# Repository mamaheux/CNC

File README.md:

# CNC
This is a project to learn how to create a 3-axis CNC router. It contains the mechanical, electrical and software designs.

## Folder Descriptions

### CAD
This folder contains the CAD files to build the CNC. It is built from aluminium extrusions and 3D printed parts.

### control
This folder contains the graphical user interface for controlling the CNC from a computer.

### electronics/teensy
This folder contains the PCB design of the board controlling the stepper drivers, endstops, and spindle drive.

### firmware
This folder contains the firmware that parses the G-code to control the spindle speed and the stepper motors using a trapezoidal velocity profile.

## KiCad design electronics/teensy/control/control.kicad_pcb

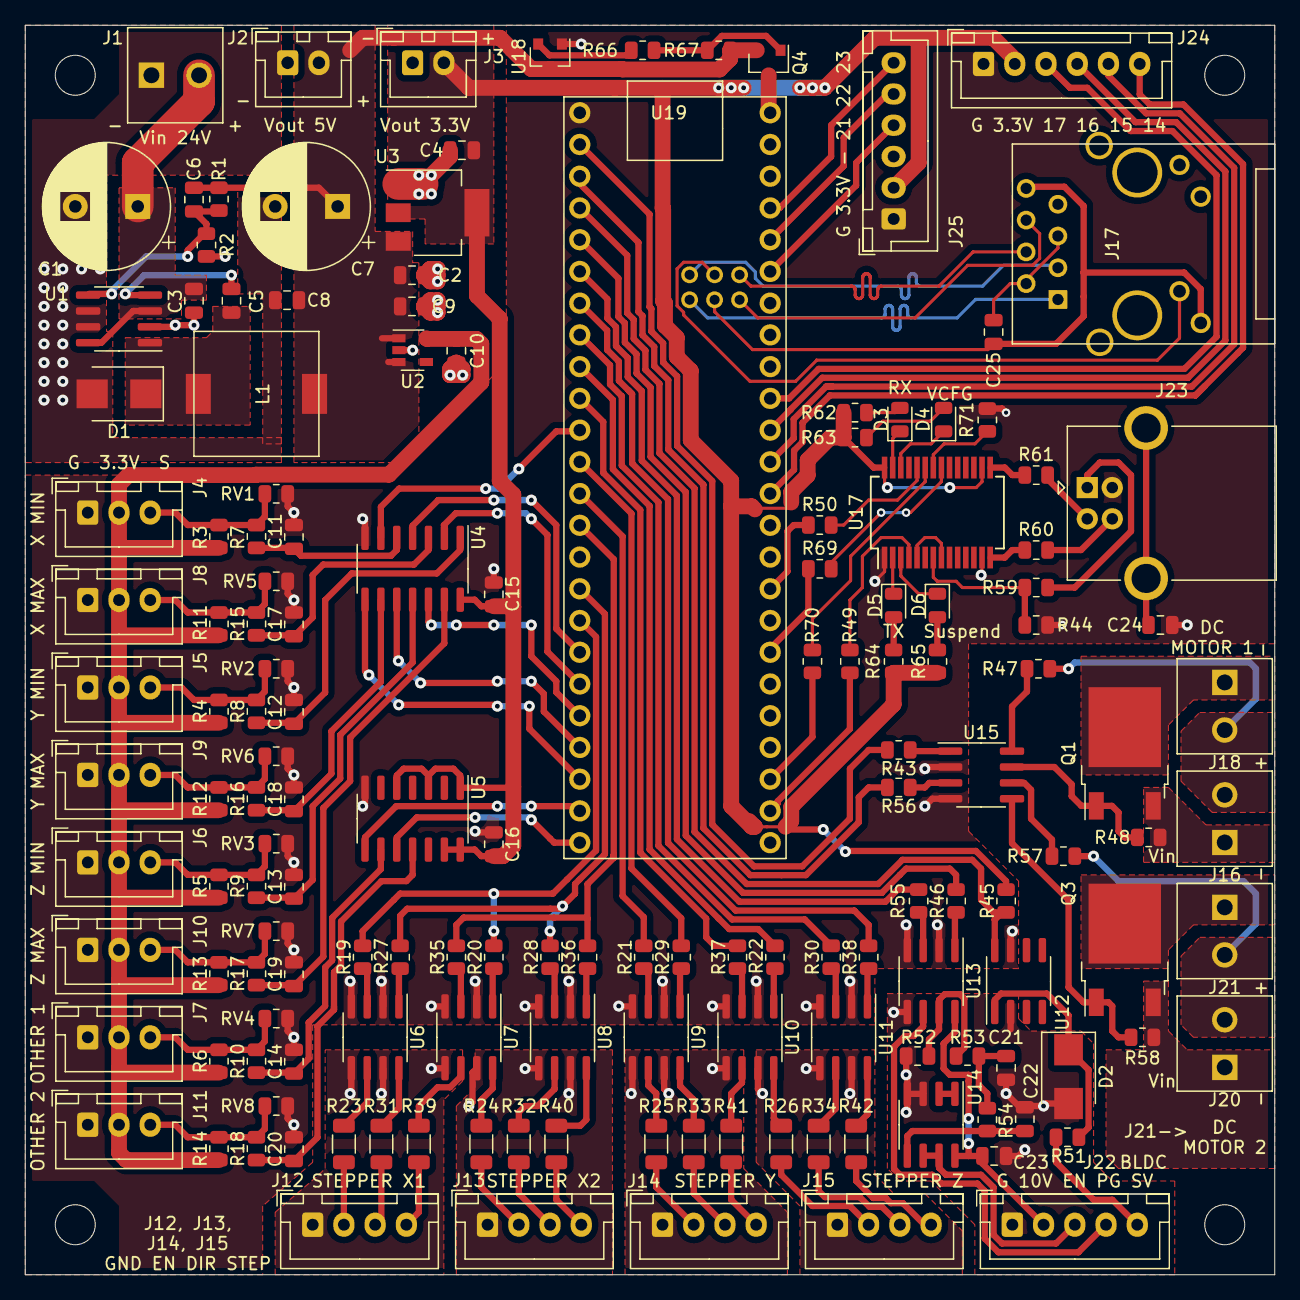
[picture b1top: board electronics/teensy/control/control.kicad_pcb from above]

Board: 2 copper layers, 100.0 x 100.0 mm, 156 parts (1 on the bottom side), 153 nets.

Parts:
C1: 33µF/35V; CP_Radial_D10.0mm_P5.00mm
C2: 10µF/10V/Low ESL; C_0805_2012Metric
C3, C9, C10, C23: 1µF/35V; C_0805_2012Metric
C4: 22µF/10V/Low ESL; C_0805_2012Metric
C5: 0.33µF; C_0805_2012Metric
C6, C11, C12, C13, C14, C15, C16, C17, C18, C19, C20, C22, C25: 0.1µF/25V; C_0805_2012Metric
C7: 330µF/10V; CP_Radial_D10.0mm_P5.00mm
C8: 2.2µF/35V; C_0805_2012Metric
C21: 47nF/25V; C_0805_2012Metric
C24: 4700pF; C_0805_2012Metric
D1, D2: B340AE-13; D_SMB
D3: ORANGE; D_0805_2012Metric
D4: GREEN; D_0805_2012Metric
D5: BLUE; D_0805_2012Metric
D6: RED; D_0805_2012Metric
J1: Vin 24V; EBWA-02-B
J2: Vout 5V; JST_XH_B2B-XH-A_1x02_P2.50mm_Vertical
J3: Vout 3.3V; JST_XH_B2B-XH-A_1x02_P2.50mm_Vertical
J4: X_MIN; JST_XH_B3B-XH-A_1x03_P2.50mm_Vertical
J5: Y_MIN; JST_XH_B3B-XH-A_1x03_P2.50mm_Vertical
J6: Z_MIN; JST_XH_B3B-XH-A_1x03_P2.50mm_Vertical
J7: OTHER 1; JST_XH_B3B-XH-A_1x03_P2.50mm_Vertical
J8: X_MAX; JST_XH_B3B-XH-A_1x03_P2.50mm_Vertical
J9: Y_MAX; JST_XH_B3B-XH-A_1x03_P2.50mm_Vertical
J10: Z_MAX; JST_XH_B3B-XH-A_1x03_P2.50mm_Vertical
J11: OTHER_2; JST_XH_B3B-XH-A_1x03_P2.50mm_Vertical
J12, J14, J15: Stepper X1; JST_XH_B4B-XH-A_1x04_P2.50mm_Vertical
J13: Stepper X2; JST_XH_B4B-XH-A_1x04_P2.50mm_Vertical
J16, J20: DC Motor Vin 24V; EBWA-02-B
J17: Cetus_J1B1211CCD; Cetus J1B1211CCD
J18, J21: DC Motor; EBWA-02-B
J22: SPINDLE_BLDC_CONTROLLER; JST_XH_B5B-XH-A_1x05_P2.50mm_Vertical
J23: USB_B; USB_B_OST_USB-B1HSxx_Horizontal
J24, J25: EXT; JST_XH_B6B-XH-A_1x06_P2.50mm_Vertical
L1: 68µH/Sumida CDRH104R-680MC; CDRH104RNP-680NC
Q1, Q3: TK1R4S04PB; TO-252-2
Q4: SI2301CDS-T1-E3; SOT-23
R1: 3.01k; R_0805_2012Metric
R2: 976; R_0805_2012Metric
R3, R4, R5, R6, R7, R8, R9, R10, R11, R12, R13, R14, R15, R16, R17, R18, R45, R47, R48, R57, R58, R59, R66: 10k; R_0805_2012Metric
R19, R20, R21, R22, R27, R28, R29, R30, R35, R36, R37, R38, R43, R46, R49, R50, R51, R55, R56, R69, R70, R71: 1k; R_0805_2012Metric
R23, R24, R25, R26, R31, R32, R33, R34, R39, R40, R41, R42: 1.82k/0.5W; R_1206_3216Metric
R44: 20k; R_0805_2012Metric
R52: 2.2k; R_0805_2012Metric
R53: 47k; R_0805_2012Metric
R54, R67: 100k; R_0805_2012Metric
R60, R61: 24; R_0805_2012Metric
R62: 174; R_0805_2012Metric
R63, R65: 150; R_0805_2012Metric
R64: 30.1; R_0805_2012Metric
R68: 0; R_1206_3216Metric
RV1, RV2, RV3, RV4, RV5, RV6, RV7, RV8: VC080503A100DP; R_0805_2012Metric
U1: MIC4684; SOIC-8_3.9x4.9mm_P1.27mm
U2: AP7354-33W5-7; SOT-23-5
U3: AZ1117IH-3.3TRG1; SOT-223-3_TabPin2
U4, U5: SN74LVC14ADRG3; SOIC-14_3.9x8.7mm_P1.27mm
U6, U7, U8, U9, U10, U11, U12, U13, U15: MOCD217R2M; SOIC-8_3.9x4.9mm_P1.27mm
U14: TS912; SOIC-8_3.9x4.9mm_P1.27mm
U17: CY7C64225; SSOP-28_5.3x10.2mm_P0.65mm
U18: LM810M3-4.63; SOT-23
U19: Teensy_4.1; Teensy 4.1

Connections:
+3V3: C4.1, C15.1, C16.1, J3.2, J24.2, J25.2, R45.2, R62.1, R63.1, R64.1, R65.1, U3.2, U4.14, U5.1, U5.3, U5.5, U5.13, U5.14, U17.16, U17.28
+3V3_LSW: C10.1, J4.2, J5.2, J6.2, J7.2, J8.2, J9.2, J10.2, J11.2, R3.1, R4.1, R5.1, R6.1, R11.1, R12.1, R13.1, R14.1, U2.5
+5V: C2.1, C6.1, C7.1, C8.1, C9.1, J2.2, L1.2, Q4.2, R1.1, R67.2, U2.1, U2.3, U3.3, U18.3
+24V: C1.1, C3.1, J1.2, U1.3, U1.8
/endstops/X_MAX: U4.4, U19.26
/endstops/X_MIN: U4.6, U19.9
/endstops/Y_MAX: U4.8, U19.30
/endstops/Y_MIN: U4.2, U19.27
/endstops/Z_MAX: U4.12, U19.28
/endstops/Z_MIN: U4.10, U19.29
/mcu/BLDC_MOTOR_PWM: R46.2, U19.3
/mcu/DC_MOTOR_PWM_1: R43.2, U19.0
/mcu/DC_MOTOR_PWM_2: R56.2, U19.1
/mcu/ETH_GND: C25.2, J17.8, J17.9, U19.ETH_GND
/mcu/ETH_LED: J17.10, U19.ETH_LED
/mcu/ETH_RX+: J17.4, U19.ETH_RX+
/mcu/ETH_RX-: J17.6, U19.ETH_RX-
/mcu/ETH_TX+: J17.1, U19.ETH_TX+
/mcu/ETH_TX-: J17.3, U19.ETH_TX-
/mcu/OTHER_1_ENDSTOP: U5.8, U19.31
/mcu/OTHER_2_ENDSTOP: U5.10, U19.32
/mcu/PIN_14: J24.6, U19.14
/mcu/PIN_15: J24.5, U19.15
/mcu/PIN_16: J24.4, U19.16
/mcu/PIN_17: J24.3, U19.17
/mcu/PIN_21: J25.4, U19.21
/mcu/PIN_22: J25.5, U19.22
/mcu/PIN_23: J25.6, U19.23
/mcu/USB_UART_CTS: R69.1, U19.39
/mcu/USB_UART_RTS: R50.1, U19.41
/mcu/USB_UART_RX: R70.1, U19.35
/mcu/USB_UART_TX: R49.1, U19.34
/spindle/BLDC_CONTROLLER_10V: C23.1, J22.2, U13.8, U14.8
/spindle/BLDC_CONTROLLER_EN: J22.4, U13.6
/spindle/BLDC_CONTROLLER_GND: C21.2, C22.2, C23.2, D2.2, J22.1, R52.2, U12.2, U13.5, U14.3, U14.4
/spindle/BLDC_CONTROLLER_PG: J22.5, R51.1
/spindle/BLDC_CONTROLLER_SV: J22.3, U14.6, U14.7
/spindle/BLDC_EN: R55.2, U19.4
/spindle/BLDC_FEEDBACK: R45.1, U12.8, U19.2
/spindle/DC_MOTOR_24V_1: J16.2, J18.2, R47.2
/spindle/DC_MOTOR_24V_2: J20.2, J21.2, R57.2
/spindle/DC_MOTOR_GND_1: J16.1, Q1.3, R48.1
/spindle/DC_MOTOR_GND_2: J20.1, Q3.3, R58.1
/steppers/OPTO_X_DIR_1: J12.3, R31.1
/steppers/OPTO_X_DIR_2: J13.3, R32.1
/steppers/OPTO_X_EN_1: J12.2, R23.1
/steppers/OPTO_X_EN_2: J13.2, R24.1
/steppers/OPTO_X_GND_1: J12.1, U6.5, U6.7, U7.5
/steppers/OPTO_X_GND_2: J13.1, U7.7, U8.5, U8.7
/steppers/OPTO_X_STEP_1: J12.4, R39.1
/steppers/OPTO_X_STEP_2: J13.4, R40.1
/steppers/OPTO_Y_DIR: J14.3, R33.1
/steppers/OPTO_Y_EN: J14.2, R25.1
/steppers/OPTO_Y_GND: J14.1, U9.5, U9.7, U10.5
/steppers/OPTO_Y_STEP: J14.4, R41.1
/steppers/OPTO_Z_DIR: J15.3, R34.1
/steppers/OPTO_Z_EN: J15.2, R26.1
/steppers/OPTO_Z_GND: J15.1, U10.7, U11.5, U11.7
/steppers/OPTO_Z_STEP: J15.4, R42.1
/steppers/X_DIR: R27.2, R28.2, U19.24
/steppers/X_EN: R19.2, R20.2, U19.25
/steppers/X_STEP: R35.2, R36.2, U19.12
/steppers/Y_DIR: R29.2, U19.10
/steppers/Y_EN: R21.2, U19.11
/steppers/Y_STEP: R37.2, U19.8
/steppers/Z_DIR: R30.2, U19.6
/steppers/Z_EN: R22.2, U19.7
/steppers/Z_STEP: R38.2, U19.5
GNDD: C11.2, C12.2, C13.2, C14.2, C15.2, C16.2, C17.2, C18.2, C19.2, C20.2, C24.2, J4.1, J5.1, J6.1, J7.1, J8.1, J9.1, J10.1, J11.1, J23.4, J24.1, J25.1, R44.2, R68.2, R71.2, RV1.1, RV2.1, RV3.1, RV4.1, RV5.1, RV6.1, RV7.1, RV8.1, U4.7, U5.7, U6.2, U6.4, U7.2, U7.4, U8.2, U8.4, U9.2, U9.4, U10.2, U10.4, U11.2, U11.4, U12.7, U13.2, U13.4, U15.2, U15.4, U17.1, U17.13, U18.1, U19.GND_0
GNDPWR: C1.2, C2.2, C3.2, C4.2, C7.2, C8.2, C9.2, C10.2, D1.2, J1.1, J2.1, J3.1, R2.2, R68.1, U1.2, U1.6, U1.7, U2.2, U3.1
unnamed: C5.1, U1.4
unnamed: C5.2, D1.1, L1.1, U1.1
unnamed: C6.2, R1.2, R2.1, U1.5
unnamed: C11.1, R7.1, U4.5
unnamed: C12.1, R8.1, U4.1
unnamed: C13.1, R9.1, U4.11
unnamed: C14.1, R10.1, U5.9
unnamed: C17.1, R15.1, U4.3
unnamed: C18.1, R16.1, U4.9
unnamed: C19.1, R17.1, U4.13
unnamed: C20.1, R18.1, U5.11
unnamed: C21.1, R53.1, R54.2
unnamed: C22.1, R54.1, U14.5
unnamed: C24.1, J23.5
unnamed: C25.1, J17.2, J17.5
unnamed: D2.1, R51.2, U12.1
unnamed: D3.1, U17.27
unnamed: D3.2, R62.2
unnamed: D4.1, U17.26
unnamed: D4.2, R63.2
unnamed: D5.1, U17.2
unnamed: D5.2, R64.2
unnamed: D6.1, U17.3
unnamed: D6.2, R65.2
unnamed: J4.3, R3.2, R7.2, RV1.2
unnamed: J5.3, R4.2, R8.2, RV2.2
unnamed: J6.3, R5.2, R9.2, RV3.2
unnamed: J7.3, R6.2, R10.2, RV4.2
unnamed: J8.3, R11.2, R15.2, RV5.2
unnamed: J9.3, R12.2, R16.2, RV6.2
unnamed: J10.3, R13.2, R17.2, RV7.2
unnamed: J11.3, R14.2, R18.2, RV8.2
unnamed: J18.1, Q1.2
unnamed: J21.1, Q3.2
unnamed: J23.1, R59.2
unnamed: J23.2, R61.2
unnamed: J23.3, R60.2
unnamed: Q1.1, R48.2, U15.7
unnamed: Q3.1, R58.2, U15.5
unnamed: Q4.1, R66.1, R67.1
unnamed: Q4.3, U19.Vin
unnamed: R19.1, U6.3
unnamed: R20.1, U7.1
unnamed: R21.1, U9.3
unnamed: R22.1, U10.1
unnamed: R23.2, U6.6
unnamed: R24.2, U7.8
unnamed: R25.2, U9.6
unnamed: R26.2, U10.8
unnamed: R27.1, U6.1
unnamed: R28.1, U8.3
unnamed: R29.1, U9.1
unnamed: R30.1, U11.3
unnamed: R31.2, U6.8
unnamed: R32.2, U8.6
unnamed: R33.2, U9.8
unnamed: R34.2, U11.6
unnamed: R35.1, U7.3
unnamed: R36.1, U8.1
unnamed: R37.1, U10.3
unnamed: R38.1, U11.1
unnamed: R39.2, U7.6
unnamed: R40.2, U8.8
unnamed: R41.2, U10.6
unnamed: R42.2, U11.8
unnamed: R43.1, U15.1
unnamed: R44.1, R59.1, U17.7
unnamed: R46.1, U13.1
unnamed: R47.1, U15.8
unnamed: R49.2, U17.4
unnamed: R50.2, U17.24
unnamed: R52.1, R53.2, U13.7
unnamed: R55.1, U13.3
unnamed: R56.1, U15.3
unnamed: R57.1, U15.6
unnamed: R60.1, U17.14
unnamed: R61.1, U17.15
unnamed: R66.2, U18.2
unnamed: R69.2, U17.21
unnamed: R70.2, U17.23
unnamed: R71.1, U17.22
unnamed: U14.1, U14.2
unnamed: U17.5, U17.8

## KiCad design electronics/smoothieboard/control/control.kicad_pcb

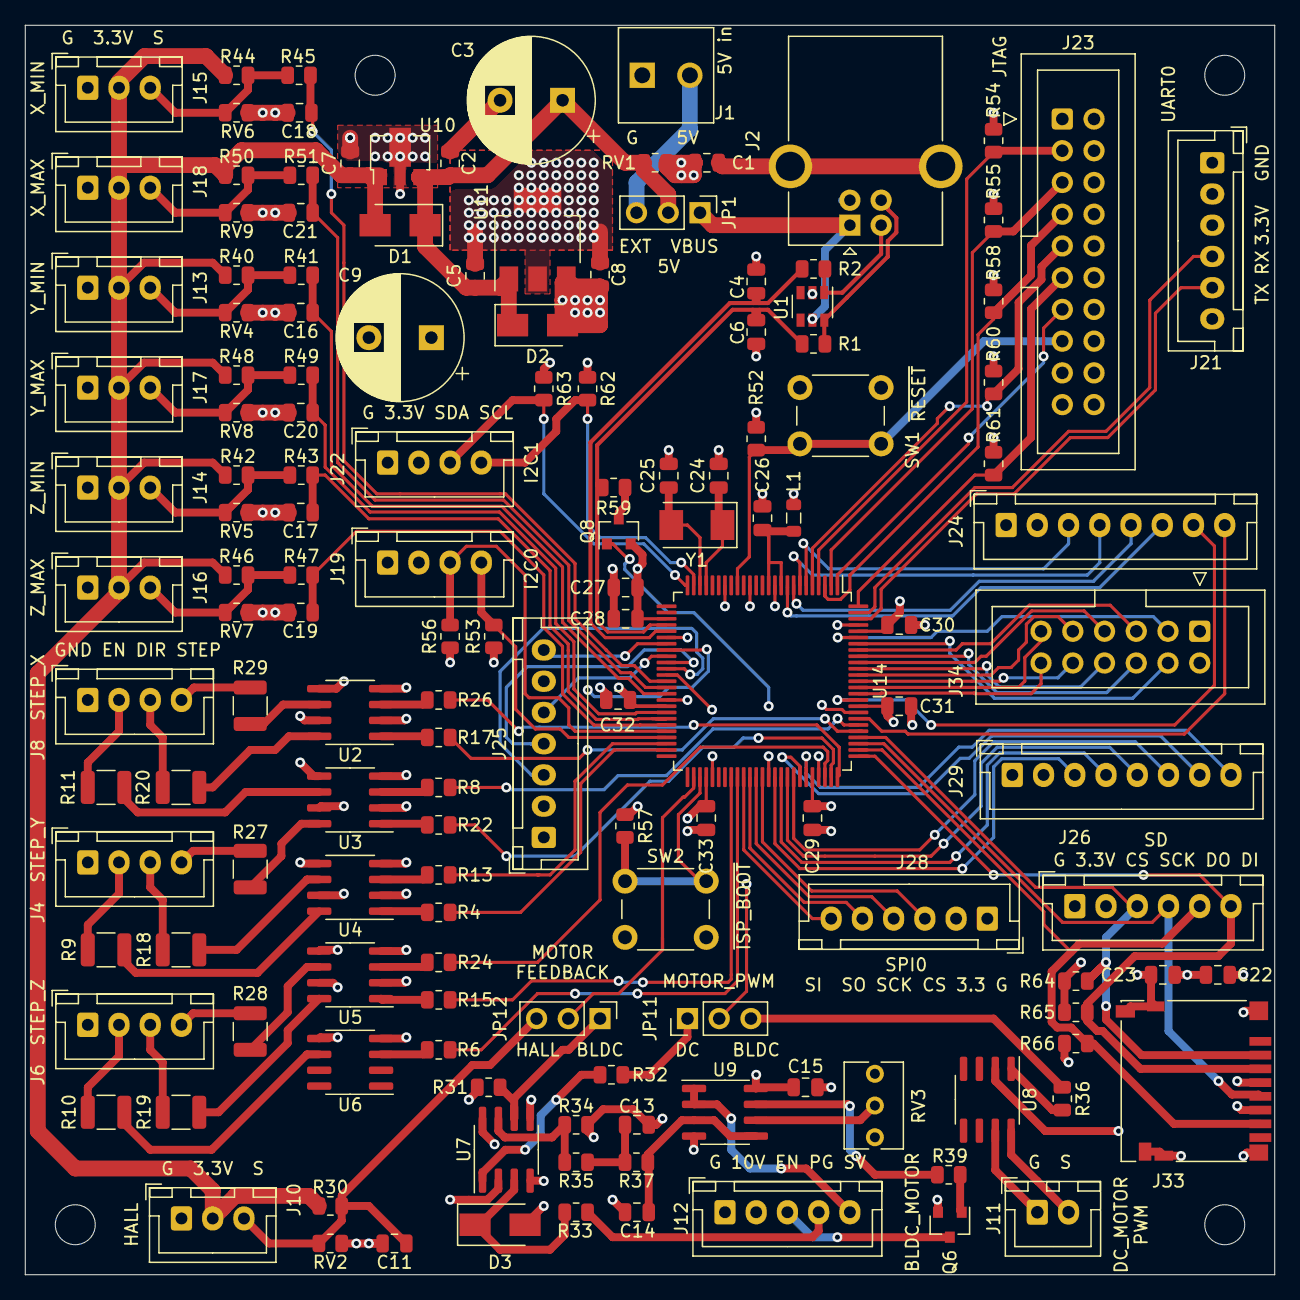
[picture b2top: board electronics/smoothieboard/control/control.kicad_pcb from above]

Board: 4 copper layers, 100.0 x 100.0 mm, 145 parts (0 on the bottom side), 138 nets.

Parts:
C1: 4700pF; C_0805_2012Metric
C2, C15, C23: 1µF/20V; C_0805_2012Metric
C3, C9: 1000µF/20V; CP_Radial_D10.0mm_P5.00mm
C4, C6: 18pF/20V; C_0805_2012Metric
C5, C14, C16, C17, C18, C19, C20, C21, C22, C28, C29, C30, C31, C32, C33: 0.1µF/20V; C_0805_2012Metric
C7: 2.2µF/20V; C_0805_2012Metric
C8, C27: 10µF/20V; C_0805_2012Metric
C11: 10pF/20V; C_0805_2012Metric
C13: 47nF/20V; C_0805_2012Metric
C24, C25: 12pF/AC; C_0805_2012Metric
C26: 1µF/10V; C_0805_2012Metric
D1, D2, D3: S1B-13-F; D_SMA
J1: 5V; EBWA-02-B
J2: USB_B; USB_B_OST_USB-B1HSxx_Horizontal
J4: JST_OPTO_Y; JST_XH_B4B-XH-A_1x04_P2.50mm_Vertical
J6: JST_OPTO_Z; JST_XH_B4B-XH-A_1x04_P2.50mm_Vertical
J8: JST_OPTO_X; JST_XH_B4B-XH-A_1x04_P2.50mm_Vertical
J10: A3213EUA-T; JST_XH_B3B-XH-A_1x03_P2.50mm_Vertical
J11: MOTOR; JST_XH_B2B-XH-A_1x02_P2.50mm_Vertical
J12: SPINDLE_BLDC_CONTROLLER; JST_XH_B5B-XH-A_1x05_P2.50mm_Vertical
J13: JST_Y_MIN; JST_XH_B3B-XH-A_1x03_P2.50mm_Vertical
J14: JST_Z_MIN; JST_XH_B3B-XH-A_1x03_P2.50mm_Vertical
J15: JST_X_MIN; JST_XH_B3B-XH-A_1x03_P2.50mm_Vertical
J16: JST_Z_MAX; JST_XH_B3B-XH-A_1x03_P2.50mm_Vertical
J17: JST_Y_MAX; JST_XH_B3B-XH-A_1x03_P2.50mm_Vertical
J18: JST_X_MAX; JST_XH_B3B-XH-A_1x03_P2.50mm_Vertical
J19: I2C0; JST_XH_B4B-XH-A_1x04_P2.50mm_Vertical
J21: UART0; JST_XH_B6B-XH-A_1x06_P2.50mm_Vertical
J22: I2C1; JST_XH_B4B-XH-A_1x04_P2.50mm_Vertical
J23: JTAG; IDC-Header_2x10_P2.54mm_Vertical
J24, J29: IO; JST_XH_B8B-XH-A_1x08_P2.50mm_Vertical
J25: IO; JST_XH_B7B-XH-A_1x07_P2.50mm_Vertical
J26: SD_CARD_SIGNALS; JST_XH_B6B-XH-A_1x06_P2.50mm_Vertical
J28: SPI0; JST_XH_B6B-XH-A_1x06_P2.50mm_Vertical
J33: MICROSD_CARD; microSD_HC_Hirose_DM3D-SF
J34: ETHERNET; IDC-Header_2x06_P2.54mm_Vertical
JP1: 5V; PinHeader_1x03_P2.54mm_Vertical
JP11, JP12: Jumper_3_Open; PinHeader_1x03_P2.54mm_Vertical
L1: 10 µH; L_0805_2012Metric
Q6: 2N7002-7-F; SOT-23
Q8: BSS84; SOT-23
R1, R2: 33; R_0805_2012Metric
R4, R6, R8, R13, R15, R17, R22, R24, R26, R32, R33, R36, R40, R42, R44, R46, R48, R50: 1k; R_0805_2012Metric
R9, R10, R11, R18, R19, R20, R27, R28, R29: 1.82k/0.5W; R_1210_3225Metric
R30: 50k; R_0805_2012Metric
R31, R52, R54, R55, R57, R58, R60, R61, R64, R65, R66: 10k; R_0805_2012Metric
R34, R53, R56, R62, R63: 2.2k; R_0805_2012Metric
R35: 47k; R_0805_2012Metric
R37: 100k; R_0805_2012Metric
R39: 200; R_0805_2012Metric
R41, R43, R45, R47, R49, R51: 5.62k; R_0805_2012Metric
R59: 1.5k; R_0805_2012Metric
RV1: B72510T0040M062; R_0805_2012Metric
RV2, RV4, RV5, RV6, RV7, RV8, RV9: VC080503A100DP; R_0805_2012Metric
RV3: POT_10k; Potentiometer_Bourns_3266Y_Vertical
SW1, SW2: SW_Push; SW_PUSH_6mm_H5mm
U1: NUP2114UCMR6T1G; SOT-23-6
U2, U3, U4, U5, U6, U7, U8: MOCD217R2M; SOIC-8_3.9x4.9mm_P1.27mm
U9: TS912; SOIC-8_3.9x4.9mm_P1.27mm
U10: AP7381_SOT89; SOT-89-3
U11: LM2937IMP-3.3; SOT-223-3_TabPin2
U14: LPC1769FBD100; LQFP-100_14x14mm_P0.5mm
Y1: 12MHz; Crystal_SMD_Abracon_ABM3-2Pin_5.0x3.2mm

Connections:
+3V3: C8.1, C9.1, C22.1, C23.1, C27.2, C28.2, C29.2, C30.2, C31.2, C32.2, C33.2, D2.2, J19.2, J21.3, J22.2, J24.2, J25.2, J26.2, J28.2, J29.2, J33.4, J34.2, L1.1, Q8.2, R31.1, R52.1, R53.1, R54.1, R55.1, R56.1, R57.1, R58.1, R61.1, R62.1, R63.1, R64.1, R65.1, R66.1, U11.3, U14.19, U14.28, U14.42, U14.54, U14.71, U14.84, U14.96
+5V: C2.1, C3.1, C5.1, D1.1, D2.1, JP1.2, RV1.1, U10.3, U11.1
/J2_D+: J2.3, R1.1, U1.6
/J2_D-: J2.2, R2.1, U1.1
/endstops/X_MAX: C21.1, R51.2, U14.39
/endstops/X_MIN: C18.1, R45.2, U14.38
/endstops/Y_MAX: C20.1, R49.2, U14.43
/endstops/Y_MIN: C16.1, R41.2, U14.40
/endstops/Z_MAX: C19.1, R47.2, U14.45
/endstops/Z_MIN: C17.1, R43.2, U14.44
/mcu/ENET_CRS: J34.6, U14.92
/mcu/ENET_MDC: J34.11, U14.87
/mcu/ENET_MDIO: J34.12, U14.86
/mcu/ENET_REF_CLK: J34.10, U14.88
/mcu/ENET_RXD0: J34.7, U14.91
/mcu/ENET_RXD1: J34.8, U14.90
/mcu/ENET_RX_ER: J34.9, U14.89
/mcu/ENET_TXD0: J34.3, U14.95
/mcu/ENET_TXD1: J34.4, U14.94
/mcu/ENET_TX_EN: J34.5, U14.93
/mcu/I2C0_SCL: J19.4, R53.2, U14.47
/mcu/I2C0_SDA: J19.3, R56.2, U14.46
/mcu/I2C1_SCL: J22.4, R62.2, U14.24
/mcu/I2C1_SDA: J22.3, R63.2, U14.25
/mcu/JTAG_RTCK: J23.11, R61.2, U14.100
/mcu/JTAG_TCK: J23.9, R60.2, U14.5
/mcu/JTAG_TDI: J23.5, R55.2, U14.2
/mcu/JTAG_TDO: J23.13, U14.1
/mcu/JTAG_TMS: J23.7, R58.2, U14.3
/mcu/P1_18: J25.7, U14.32
/mcu/P1_19: J25.6, U14.33
/mcu/P1_20: J25.5, U14.34
/mcu/P1_21: J25.4, U14.35
/mcu/P1_22: J25.3, U14.36
/mcu/P2_3: J29.8, U14.70
/mcu/P2_4: J29.7, U14.69
/mcu/P2_5: J29.6, U14.68
/mcu/P2_6: J29.5, U14.67
/mcu/P2_7: J29.4, U14.66
/mcu/P2_8: J29.3, U14.65
/mcu/P4_28: J24.8, U14.82
/mcu/P4_29: J24.7, U14.85
/mcu/PO_23: J24.6, U14.9
/mcu/PO_24: J24.5, U14.8
/mcu/PO_25: J24.4, U14.7
/mcu/PO_26: J24.3, U14.6
/mcu/SCON: Q8.1, U14.64
/mcu/SD_CS: J26.3, J33.2, R64.2, U14.79
/mcu/SD_MISO: J26.5, J33.7, R66.2, U14.77
/mcu/SD_MOSI: J26.6, J33.3, R65.2, U14.76
/mcu/SD_SCK: J26.4, J33.5, U14.78
/mcu/SPI0_MISO: J28.5, U14.61
/mcu/SPI0_MOSI: J28.6, U14.60
/mcu/SPI0_SCK: J28.4, U14.62
/mcu/SPI0_SSEL: J28.3, U14.63
/mcu/UART0_RX: J21.4, U14.99
/mcu/UART0_TX: J21.5, U14.98
/mcu/USB_D+: C6.1, R1.2, R59.2, U14.29
/mcu/USB_D-: C4.1, R2.2, U14.30
/mcu/X_DIR: R17.2, U14.80
/mcu/X_EN: R8.2, U14.81
/mcu/X_STEP: R26.2, U14.75
/mcu/Y_DIR: R13.2, U14.48
/mcu/Y_EN: R4.2, U14.49
/mcu/Y_STEP: R22.2, U14.74
/mcu/Z_DIR: R15.2, U14.58
/mcu/Z_EN: R6.2, U14.59
/mcu/Z_STEP: R24.2, U14.73
/mcu/~ISP_BOOT: R57.2, SW2.1, U14.53
/mcu/~JTAG_TRST: J23.3, R54.2, U14.4
/mcu/~RESET: J23.15, R52.2, SW1.1, U14.17
/spindle/BLDC_FEEDBACK: JP12.1, R31.2, U7.6
/spindle/BLDC_PWM: JP11.1, R32.1
/spindle/CONTROLLER_10V: C15.1, J12.2, RV3.1, U7.8, U9.8
/spindle/CONTROLLER_EN: J12.3, Q6.3
/spindle/CONTROLLER_GND: C13.2, C14.2, C15.2, D3.2, J12.1, Q6.2, R34.2, RV3.3, U7.4, U9.4
/spindle/CONTROLLER_PG: J12.4, R33.2
/spindle/CONTROLLER_SV: J12.5, U9.1, U9.2
/spindle/DC_PWM: JP11.3, R36.1
/spindle/FEEDBACK: JP12.2, U14.52
/spindle/HALL_EFFECT_FEEDBACK: C11.1, J10.3, JP12.3, R30.1, RV2.2
/spindle/PWM: JP11.2, U14.37
/steppers/OPTO_X_DIR: J8.3, R20.2
/steppers/OPTO_X_EN: J8.2, R11.2
/steppers/OPTO_X_GND: J8.1, U2.5, U2.7, U3.5
/steppers/OPTO_X_STEP: J8.4, R29.2
/steppers/OPTO_Y_DIR: J4.3, R18.2
/steppers/OPTO_Y_EN: J4.2, R9.2
/steppers/OPTO_Y_GND: J4.1, U3.7, U4.5, U4.7
/steppers/OPTO_Y_STEP: J4.4, R27.2
/steppers/OPTO_Z_DIR: J6.3, R19.2
/steppers/OPTO_Z_EN: J6.2, R10.2
/steppers/OPTO_Z_GND: J6.1, U5.5, U5.7, U6.5
/steppers/OPTO_Z_STEP: J6.4, R28.2
ENDSTOPS_3.3V: C7.1, D1.2, J10.2, J13.2, J14.2, J15.2, J16.2, J17.2, J18.2, R30.2, R40.2, R42.2, R44.2, R46.2, R48.2, R50.2, U10.1
GNDD: C1.2, C2.2, C3.2, C4.2, C5.2, C6.2, C7.2, C8.2, C9.2, C11.2, C16.2, C17.2, C18.2, C19.2, C20.2, C21.2, C22.2, C23.2, C24.2, C25.2, C26.2, C27.1, C28.1, C29.1, C30.1, C31.1, C32.1, C33.1, J1.1, J2.4, J10.1, J13.1, J14.1, J15.1, J16.1, J17.1, J18.1, J19.1, J21.1, J22.1, J23.4, J23.6, J23.8, J23.10, J23.12, J23.14, J23.16, J23.18, J23.20, J24.1, J25.1, J26.1, J28.1, J29.1, J33.6, J33.9, J33.10, J33.11, J34.1, R60.1, RV1.2, RV2.1, RV4.1, RV5.1, RV6.1, RV7.1, RV8.1, RV9.1, SW1.2, SW2.2, U1.2, U2.2, U2.4, U3.2, U3.4, U4.2, U4.4, U5.2, U5.4, U6.4, U7.2, U7.5, U8.2, U10.2, U11.2, U14.11, U14.15, U14.31, U14.41, U14.55, U14.72, U14.83, U14.97
unnamed: C1.1, J2.5
unnamed: C13.1, R35.1, R37.2
unnamed: C14.1, R37.1, U9.3, U9.5
unnamed: C24.1, U14.22, Y1.1
unnamed: C25.1, U14.23, Y1.2
unnamed: C26.1, L1.2, U14.10, U14.12
unnamed: D3.1, R33.1, U7.3
unnamed: J1.2, JP1.3
unnamed: J11.1, U8.7
unnamed: J11.2, U8.8
unnamed: J13.3, R40.1, R41.1, RV4.2
unnamed: J14.3, R42.1, R43.1, RV5.2
unnamed: J15.3, R44.1, R45.1, RV6.2
unnamed: J16.3, R46.1, R47.1, RV7.2
unnamed: J17.3, R48.1, R49.1, RV8.2
unnamed: J18.3, R50.1, R51.1, RV9.2
unnamed: Q6.1, R39.1
unnamed: Q8.3, R59.1
unnamed: R4.1, U4.1
unnamed: R6.1, U6.3
unnamed: R8.1, U3.3
unnamed: R9.1, U4.8
unnamed: R10.1, U6.6
unnamed: R11.1, U3.6
unnamed: R13.1, U4.3
unnamed: R15.1, U5.1
unnamed: R17.1, U2.1
unnamed: R18.1, U4.6
unnamed: R19.1, U5.8
unnamed: R20.1, U2.8
unnamed: R22.1, U3.1
unnamed: R24.1, U5.3
unnamed: R26.1, U2.3
unnamed: R27.1, U3.8
unnamed: R28.1, U5.6
unnamed: R29.1, U2.6
unnamed: R32.2, U7.1
unnamed: R34.1, R35.2, U7.7
unnamed: R36.2, U8.1
unnamed: R39.2, U9.7
unnamed: RV3.2, U9.6
VBUS: J2.1, JP1.1, U1.5

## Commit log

2021-04-06 Add CAD files.
2021-04-08 Add the controller schematic.
2021-04-09 Add the PCB.
2021-10-26 Add the teensy control board
2021-10-27 Add core classes and functions.
2021-10-27 Add ResourceLock tests.
2021-10-27 Add the supported G-Codes readme
2021-10-28 Add GCode, MCode and SystemCommand parsing.
2021-10-28 Add the Kernel and Module class
2021-11-03 Add gerber files
2021-11-07 Refactoring
2021-11-08 Add CoordinateTransformer (tests are missing).
2021-11-08 Add CommandSource.
2021-11-08 Add FileSystem
2021-11-08 Add update to Kernel.
2021-11-08 Add CommandSerial.
2021-11-08 Add Stepper
2021-11-08 Add Spindle
2021-11-09 Add CoordinateTransformer tests.
2021-11-09 Add CommandFile.
2021-11-09 Fix SUPPORTED_COMMANDS.md
2021-11-14 Add BoundedQueue. Add error messages.
2021-11-15 Refactor steppers. Add Stepper Controller. Add Vector2. Add Vector3. Add FixedPoint. Add ArcConverter (tests are missing).
2021-11-16 Add ArcConverter tests.
2021-11-16 Add benchs
2021-11-16 Add a missing test (ArcConverter G53)
2021-11-25 Add comment supports in SystemCommandParser
2022-11-23 Fix G92. Add Planer, Endstops, ... class skeletons.
2022-11-25 Add control app files.
2022-11-27 Add settings to control. Connect widgets to Cnc in Control. Update firmware
2022-11-28 Add GCodeModel.
2022-11-28 Fix viewing G2 and G3. Improve GCode parsing.
2022-11-28 Fix error messages. Add the command queue.
2022-11-29 Add command checks. Handle multiline response. Improve command parsing.
2022-11-30 Add a progress dialog when opening a gcode file.
2022-12-01 Fix arc problems. Add start and stop gcode file.
2022-12-01 Add the target RPM to the rpm plot.
2022-12-03 Create a small version of the app
2022-12-03 Format
2022-12-03 Add missing explicit.
2022-12-03 Fix build
2022-12-03 Add a shutdown button
2022-12-03 Fix warning
2022-12-04 Clean up the code
2022-12-04 Remove useless files
2022-12-04 Fix spindle PID
2022-12-05 Disable buttons when the gcode file is started.
2022-12-05 Add LinearBlockExecutor. Finalize Endstops.
2022-12-06 Add CncMock
2022-12-07 Update spindle support
2022-12-08 Fix ArcConverter. Add tests. Format.
2022-12-08 Fix gcode model. Update the app style.
2022-12-09 Add calculateJunctionFeedRateInMmPerS
2022-12-10 Fix Cnc classes. Add icons
2022-12-10 Fix bugs
2022-12-10 Connect console enter to the send button.^C
2022-12-11 Fix fullscreen
2022-12-16 Add the code to generate LinearBlock.
2022-12-17 Finish the Planner class.
2022-12-17 Format + cleanup
2022-12-18 Fix errors.
2022-12-18 Fix DigitalInput::attachInterrupt
2022-12-22 Use the time between pulse to calculate the RPM instead of pulse count.
2023-01-01 Fix UI
2023-01-07 Fix Z frame rigidity
2023-01-14 Fix GCodeViewWidget
2023-01-14 Improve control
2023-01-19 Fix imperial feedrates. Add estimated duration in the control.
2023-01-27 Remove radius errors.
2023-03-31 Fix G90.1 and G91.1 invalid commands.
2023-04-05 Fix firmware and control
2023-04-05 Fix Planner
2023-08-31 Fix arc converter for house numbers.
2024-04-26 Update README.md. Add a license file.
2024-12-30 Update the config for the closed loop steppers.
2024-12-30 Fix endstops period.
